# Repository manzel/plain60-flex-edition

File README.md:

# Plain60 MKD Edition
This 60% PCB is a modified version of [Plain60 Flex Edition](https://github.com/evyd13/plain60-flex-edition) rev2.2 by [evyd13](https://github.com/evyd13).

In the German keyboard community (MKD), we were looking for a universal (in the sense of board compatibility, not layout support) flexible PCB supporting all of our 60% boards. As this was not available, we used a Plain60 Flex Edition as basis, removed some holes (layout options, that is) we deemed unnecessary, and added some in other places (cutouts). The result of this is the Plain60 MKD Edition available here.

We went for even less layout support, making a tsangan (7u) bottom row the only choice. Additionally, support for ANSI and ISO is not included in a single PCB, but two variants. A third (HHKB) variant was specifically created to fit the Kara, which does not exhibit any layout options except for normal or stepped Caps Lock.

Other changes include the relocation of the microcontroller to below the spacebar, avoiding a stiffer spot on the left of the alpha cluster. The JST connector was moved as close to the position found on the Bakeneko PCB as possible, without changing the flex cut. For cases using a daughterboard, the PCB can be assembled without the USB connector. On the other hand, one can also omit the JST connector and use the USB-C one instead. Of course, assembling both is also possible, if your board has space for that.

This PCB is intended to be produced in 1.2 mm thickness and was only tested in this configuration. Depending on your choice of stabilizers, you may need shims (3D printed or FR4) for a *stable* fit. However, even though untested, 1.6 mm should work as well.

The files were created in KiCad 5.99 Nightly and later re-saved in 6 Stable, they will not open in KiCad 5.

## Features
 - USB-C and/or JST connector (for unified daughterboard)
 - ESD protection and fuse
 - Atmega32U4-AU
 - ISP header
 - AST1109MLTRQ speaker

## ANSI Version
In its ANSI version, the PCB supports only full left Shift and ANSI Enter. There are options for stepped or normal Caps Lock, full or split right Shift, and full or split Backspace.

## ISO Version
The ISO variant only supports split left Shift and ISO Enter. You can build with either stepped or normal Caps Lock, full or split right Shift, and full or split Backspace.

## HHKB Version
The HHKB version was made specifically for the Kara, but can of course be used in other HHKB-style compatible boards. It retains stepped or normal Caps Lock as the only layout option, while being fixed to HHKB layout otherwise.

## Production
Production files for JLCPCB (generated using the excellent [JLCKicadTools](https://github.com/matthewlai/JLCKicadTools)) are included. Part orientation in the CPL file was not checked as this seems to be automatically corrected by JLCPCB lately.

## Firmware
The needed QMK Firmware as well as VIA and Vial .hex and .json files are included in [firmware](./firmware/).

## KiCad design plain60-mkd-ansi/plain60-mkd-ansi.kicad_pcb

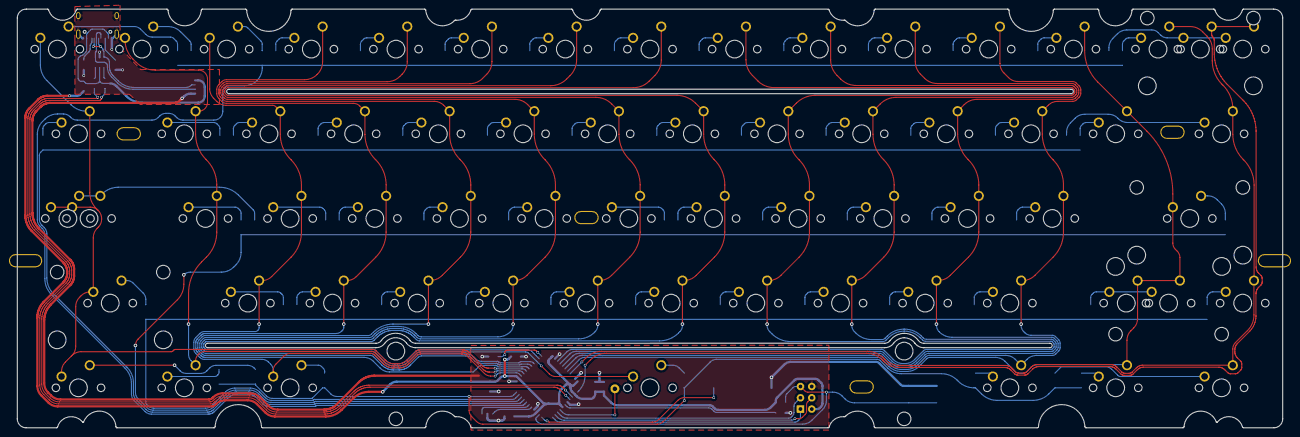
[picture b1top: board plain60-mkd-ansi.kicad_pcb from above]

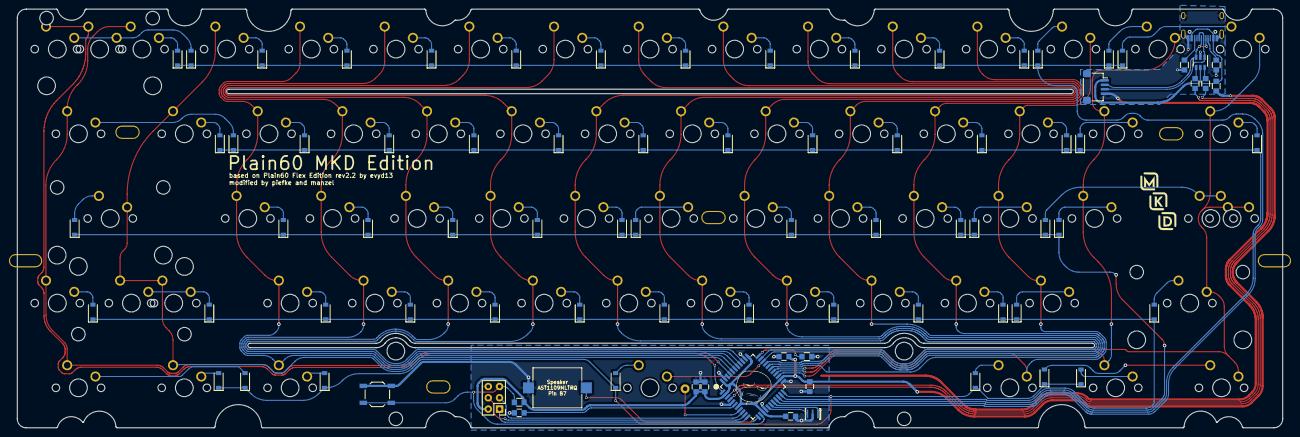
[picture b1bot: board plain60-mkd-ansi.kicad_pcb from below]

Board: 2 copper layers, 284.7 x 94.2 mm, 156 parts (85 on the bottom side), 103 nets.

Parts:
C1: 1u; C_0805
C2, C3, C4, C5: 0.1u; C_0805
C6: 4.7u; C_0805
D1, D2, D3, D4, D5, D6, D7, D8, D9, D10, D11, D12, D13, D14, D15, D16, D17, D18, D19, D20, D21, D22, D23, D24, D25, D26, D27, D28, D29, D31, D32, D33, D34, D35, D36, D37, D38, D39, D40, D41, D42, D44, D46, D48, D49, D50, D51, D52, D53, D54, D55, D56, D57, D58, D59, D61, D62, D63, D67, D72, D73, D74: D; D_SOD-123
F1: Polyfuse; R_0805
G2: LOGO; mkd-1u
H1: B0; free_pin
J1: HRO-TYPE-C-31-M-12
J2: ISP; isp_standard
J3: ai03_ud; JST_SH_SM04B-SRSS-TB_1x04-1MP_P1.00mm_Horizontal
K1, K2, K3, K4, K5, K6, K7, K8, K9, K10, K11, K12, K13, K14, K15-1, K17, K18, K19, K20, K21, K22, K23, K24, K25, K26, K27, K28, K32, K33, K34, K35, K36, K37, K38, K39, K40, K41, K42, K48, K49, K50, K51, K52, K53, K54, K55, K56, K57, K59, K62-1, K73-1: KEYSW; CHERRY_PLATE_100H
K15: KEYSW; CHERRY_PCB_200H
K16, K29, K61-1, K63-1, K72-1, K74-1: KEYSW; CHERRY_PLATE_150H
K31, K58-1: KEYSW; CHERRY_PLATE_175H
K31-1: KEYSW; CHERRY_PLATE_125H
K44, K46: KEYSW; CHERRY_PCB_225H
K58: KEYSW; CHERRY_PCB_275H
K67-1: KEYSW; CHERRY_PCB_700H_F
LS1: Speaker; speaker_AST1109MLTRQ
R1, R2: 22; R_0805
R3, R4: 5.1k; R_0805
R5, R6: 10k; R_0805
S1, S2, S3, S6: Screw; 5.5_5x2.5mm
S4, S5: Screw; 10x5_7x2.5mm
SW1: SW_PUSH; SW_SPST_TL3342
U1: ATmega32U4; ATMEGA32U4
U2: USBLC6-2SC6
X1: XTAL_GND; Resonator_SMD_muRata_CSTNExxV-3Pin-p1.2

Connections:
D+: J1.6 (DP1), J1.8 (DP2), J3.3, U2.1 (I/O1)
D-: J1.5 (DN2), J1.7 (DN1), J3.2, U2.3 (I/O2)
Da+: R1.1, U1.4 (D+)
Da-: R2.2, U1.3 (D-)
GND: C1.2, C2.1, C3.1, C4.1, C5.1, C6.1, J1.1 (GND), J1.12 (GND), J1.13 (SHIELD), J2.6, J3.4, LS1.2, R3.1, R4.2, R6.1, SW1.1, U1.5 (UGND), U1.15 (GND), U1.23 (GND), U1.35 (GND), U1.43 (GND), U2.2 (GND), X1.3
MISO: J2.1, U1.11 ((PDO/MISO/PCINT3)PB3)
MOSI: J2.4, U1.10 ((PDI/MOSI/PCINT2)PB2)
unnamed: C1.1, U1.6 (UCAP)
unnamed: D1.2 (A), K1.1
unnamed: D2.2 (A), K2.1
unnamed: D3.2 (A), K3.1
unnamed: D4.2 (A), K4.2
unnamed: D5.2 (A), K5.2
unnamed: D6.2 (A), K6.2
unnamed: D7.2 (A), K7.2
unnamed: D8.2 (A), K8.2
unnamed: D9.2 (A), K9.2
unnamed: D10.2 (A), K10.2
unnamed: D11.2 (A), K11.2
unnamed: D12.2 (A), K12.2
unnamed: D13.2 (A), K13.2
unnamed: D14.2 (A), K14.2
unnamed: D15.2 (A), K15.2, K15-1.2
unnamed: D16.2 (A), K16.2
unnamed: D17.2 (A), K17.2
unnamed: D18.2 (A), K18.2
unnamed: D19.2 (A), K19.2
unnamed: D20.2 (A), K20.2
unnamed: D21.2 (A), K21.2
unnamed: D22.2 (A), K22.2
unnamed: D23.2 (A), K23.2
unnamed: D24.2 (A), K24.2
unnamed: D25.2 (A), K25.2
unnamed: D26.2 (A), K26.2
unnamed: D27.2 (A), K27.2
unnamed: D28.2 (A), K28.2
unnamed: D29.2 (A), K29.2
unnamed: D31.2 (A), K31.1, K31-1.1
unnamed: D32.2 (A), K32.2
unnamed: D33.2 (A), K33.2
unnamed: D34.2 (A), K34.2
unnamed: D35.2 (A), K35.2
unnamed: D36.2 (A), K36.2
unnamed: D37.2 (A), K37.2
unnamed: D38.2 (A), K38.2
unnamed: D39.2 (A), K39.2
unnamed: D40.2 (A), K40.2
unnamed: D41.2 (A), K41.2
unnamed: D42.2 (A), K42.2
unnamed: D44.2 (A), K44.1
unnamed: D46.2 (A), K46.1
unnamed: D48.2 (A), K48.2
unnamed: D49.2 (A), K49.2
unnamed: D50.2 (A), K50.2
unnamed: D51.2 (A), K51.2
unnamed: D52.2 (A), K52.2
unnamed: D53.2 (A), K53.2
unnamed: D54.2 (A), K54.2
unnamed: D55.2 (A), K55.2
unnamed: D56.2 (A), K56.2
unnamed: D57.2 (A), K57.2
unnamed: D58.2 (A), K58.2, K58-1.2
unnamed: D59.2 (A), K59.2
unnamed: D61.2 (A), K61-1.1
unnamed: D62.2 (A), K62-1.2
unnamed: D63.2 (A), K63-1.1
unnamed: D67.2 (A), K67-1.1
unnamed: D72.2 (A), K72-1.2
unnamed: D73.2 (A), K73-1.2
unnamed: D74.2 (A), K74-1.2
unnamed: H1.1, U1.8 ((SS/PCINT0)PB0)
unnamed: J1.4 (CC1), R3.2
unnamed: J1.10 (CC2), R4.1
unnamed: LS1.1, U1.12 ((OC0A/OC1C/~RTS~/PCINT7)PB7)
unnamed: R1.2, U2.6 (I/O1)
unnamed: R2.1, U2.4 (I/O2)
unnamed: R6.2, U1.33 ((~HWB~)PE2)
unnamed: U1.16 (XTAL2), X1.2
unnamed: U1.17 (XTAL1), X1.1
RST: J2.5, R5.1, SW1.2, U1.13 (RESET)
SCK: J2.3, U1.9 ((SCLK/PCINT1)PB1)
VBUS: F1.2, J1.2 (VBUS), J1.11 (VBUS), J3.1, U2.5 (VBUS)
VCC: C2.2, C3.2, C4.2, C5.2, C6.2, F1.1, J2.2, R5.2, U1.2 (UVCC), U1.7 (VBUS), U1.14 (VCC), U1.24 (AVCC), U1.34 (VCC), U1.44 (AVCC)
col0: K1.2, K16.1, K31.2, K31-1.2, K46.2, K61-1.2, U1.27 ((T0/OC4D/ADC10)PD7)
col1: K2.2, K17.1, K32.1, K62-1.1, U1.26 ((T1/~OC4D~/ADC9)PD6)
col2: K3.2, K18.1, K33.1, K48.1, K63-1.2, U1.25 ((ICP2/ADC8)PD4)
col3: K4.1, K19.1, K34.1, K49.1, U1.28 ((ADC11/PCINT4)PB4)
col4: K5.1, K20.1, K35.1, K50.1, U1.29 ((ADC12/OC1A/~OC4B~/PCINT12)PB5)
col5: K6.1, K21.1, K36.1, K51.1, U1.30 ((ADC13/OC1B/OC4B/PCINT13)PB6)
col6: K7.1, K22.1, K37.1, K52.1, K67-1.2, U1.31 ((OC3A/~OC4A~)PC6)
col7: K8.1, K23.1, K38.1, K53.1, U1.32 ((ICP3/CLK0/OC4A)PC7)
col8: K9.1, K24.1, K39.1, K54.1, U1.36 ((ADC7/TDI)PF7)
col9: K10.1, K25.1, K40.1, K55.1, U1.37 ((ADC6/TDO)PF6)
col10: K11.1, K26.1, K41.1, K56.1, U1.38 ((ADC5/TMS)PF5)
col11: K12.1, K27.1, K42.1, K57.1, K72-1.1, U1.39 ((ADC4/TCK)PF4)
col12: K13.1, K28.1, K44.2, K58.1, K58-1.1, K73-1.1, U1.40 ((ADC1)PF1)
col13: K14.1, K29.1, K59.1, K74-1.1, U1.41 ((ADC0)PF0)
col14: K15.1, K15-1.1, U1.1 ((INT6/AIN0)PE6)
row0: D1.1 (K), D2.1 (K), D3.1 (K), D4.1 (K), D5.1 (K), D6.1 (K), D7.1 (K), D8.1 (K), D9.1 (K), D10.1 (K), D11.1 (K), D12.1 (K), D13.1 (K), D14.1 (K), D15.1 (K), U1.18 ((OC0B/SCL/INT0)PD0)
row1: D16.1 (K), D17.1 (K), D18.1 (K), D19.1 (K), D20.1 (K), D21.1 (K), D22.1 (K), D23.1 (K), D24.1 (K), D25.1 (K), D26.1 (K), D27.1 (K), D28.1 (K), D29.1 (K), U1.19 ((SDA/INT1)PD1)
row2: D31.1 (K), D32.1 (K), D33.1 (K), D34.1 (K), D35.1 (K), D36.1 (K), D37.1 (K), D38.1 (K), D39.1 (K), D40.1 (K), D41.1 (K), D42.1 (K), D44.1 (K), U1.20 ((RXD/INT2)PD2)
row3: D46.1 (K), D48.1 (K), D49.1 (K), D50.1 (K), D51.1 (K), D52.1 (K), D53.1 (K), D54.1 (K), D55.1 (K), D56.1 (K), D57.1 (K), D58.1 (K), D59.1 (K), U1.21 ((TXD/INT3)PD3)
row4: D61.1 (K), D62.1 (K), D63.1 (K), D67.1 (K), D72.1 (K), D73.1 (K), D74.1 (K), U1.22 ((XCK1/~CTS~)PD5)

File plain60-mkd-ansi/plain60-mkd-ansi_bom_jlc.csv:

"Comment","Designator","Footprint","LCSC Part #"
"1u","C1","C_0805","C28323"
"0.1u","C2,C3,C4,C5","C_0805","C49678"
"4.7u","C6","C_0805","C1779"
"D","D1,D2,D3,D4,D5,D6,D7,D8,D9,D10,D11,D12,D13,D14,D15,D16,D17,D18,D19,D20,D21,D22,D23,D24,D25,D26,D27,D28,D29,D31,D32,D33,D34,D35,D36,D37,D38,D39,D40,D41,D42,D44,D46,D48,D49,D50,D51,D52,D53,D54,D55,D56,D57,D58,D59,D61,D62,D63,D67,D72,D73,D74","D_SOD-123","C2099"
"Polyfuse","F1","R_0805","C261942"
"HRO-TYPE-C-31-M-12","J1","HRO-TYPE-C-31-M-12","C165948"
"ai03_ud","J3","JST_SH_SM04B-SRSS-TB_1x04-1MP_P1.00mm_Horizontal","C160404"
"Speaker","LS1","speaker_AST1109MLTRQ","C391036"
"22","R1,R2","R_0805","C17561"
"5.1k","R3,R4","R_0805","C27834"
"10k","R5,R6","R_0805","C17414"
"SW_PUSH","SW1","SW_SPST_TL3342","C92584"
"ATmega32U4","U1","ATMEGA32U4","C44854"
"USBLC6-2SC6","U2","USBLC6-2SC6","C7519"
"XTAL_GND","X1","Resonator_SMD_muRata_CSTNExxV-3Pin-p1.2","C783275"

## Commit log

2022-02-01 Initial commit of KiCad files for all three versions
2022-02-01 Adding initial readme.md
2022-02-01 Added PCB renders
2022-02-01 Updated gitignore
2022-02-02 Adding layout images
2022-02-02 Cropped PCB renders
2022-02-02 Added QMK firmware
2022-02-02 Updated for KiCad 6
2022-03-07 Updated .gitignore and added SMT files
